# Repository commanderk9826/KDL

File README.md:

국민대학교 24EV KUST 데이터로거팀

KUST Data Logger 제작 프로젝트
참여자 : 이채훈, 옹미령, 강호, 이지규

PCB제작 : 고민제

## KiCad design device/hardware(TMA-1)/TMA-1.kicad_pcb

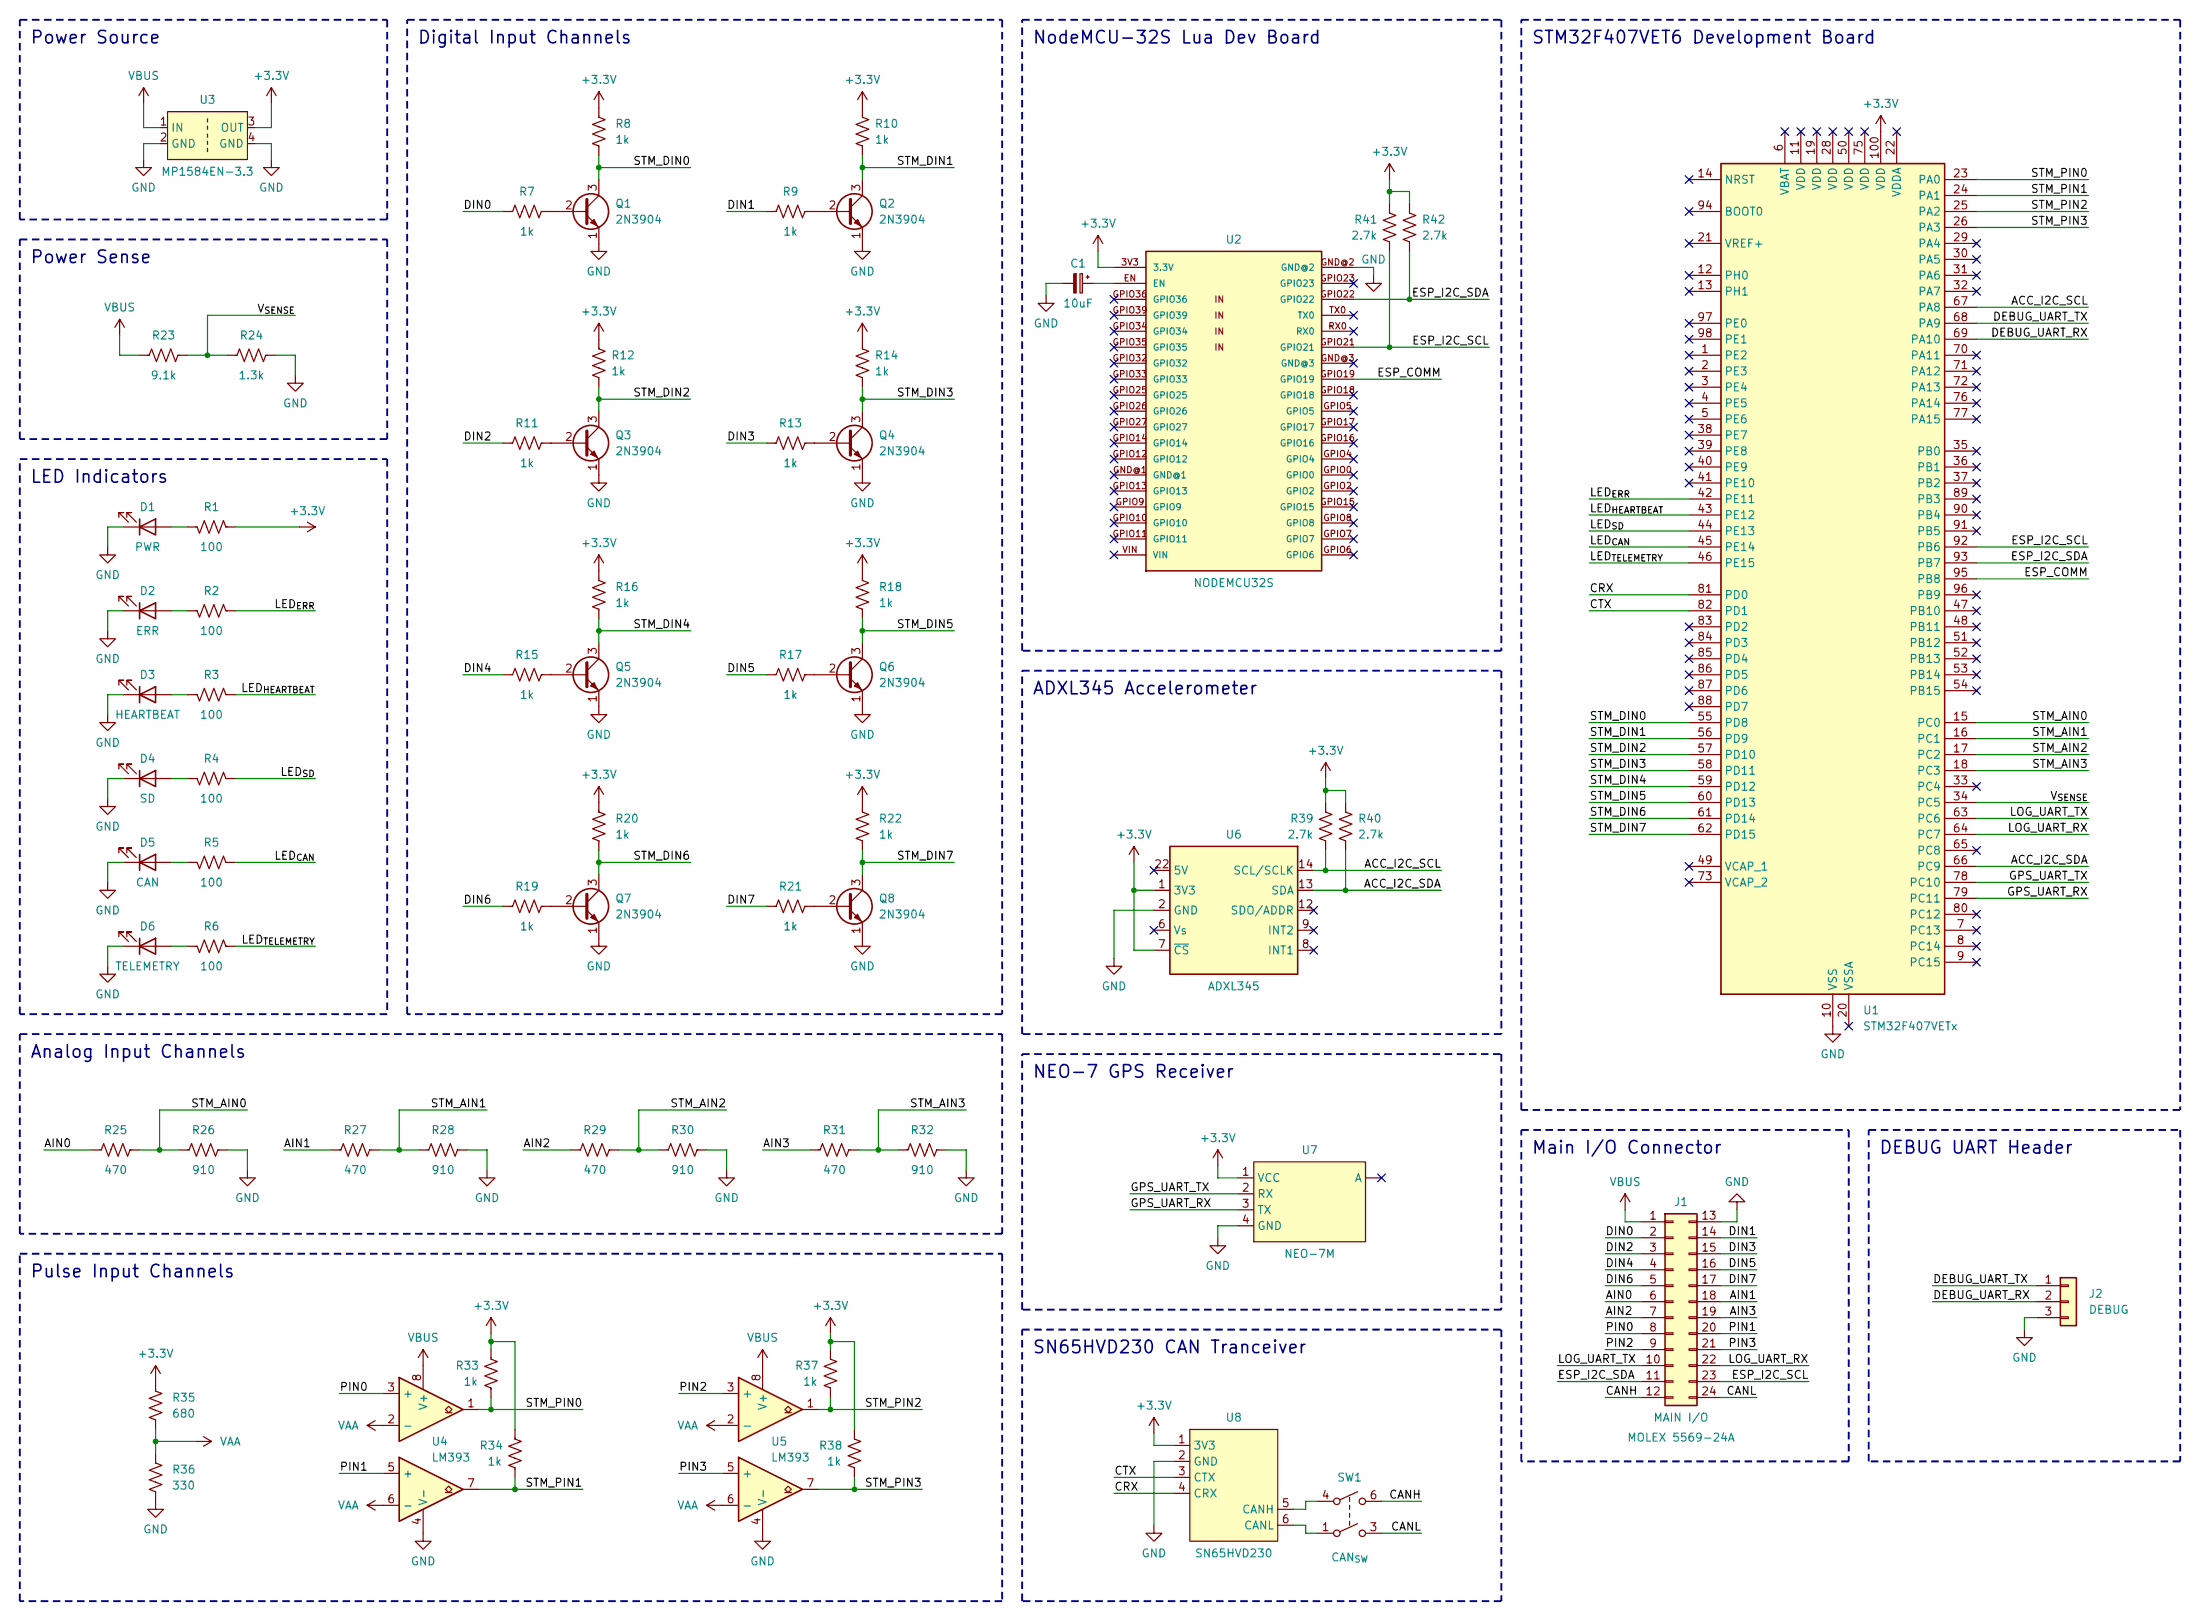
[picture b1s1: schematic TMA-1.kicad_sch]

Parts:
C1: 10uF; CP_Radial_D5.0mm_P2.00mm
D1: PWR; LED_D5.0mm_FlatTop
D2: ERR; LED_D5.0mm_FlatTop
D3: HEARTBEAT; LED_D5.0mm_FlatTop
D4: SD; LED_D5.0mm_FlatTop
D5: CAN; LED_D5.0mm_FlatTop
D6: TELEMETRY; LED_D5.0mm_FlatTop
J1: MAIN I/O; Molex_Mini-Fit_Jr_5569-24A1_2x12_P4.20mm_Horizontal
J2: DEBUG; PinHeader_1x03_P2.54mm_Vertical
Q1, Q2, Q3, Q4, Q5, Q6, Q7, Q8: 2N3904; TO-92_Inline_Wide
R1, R2, R3, R4, R5, R6: 100; R_Axial_DIN0207_L6.3mm_D2.5mm_P10.16mm_Horizontal
R7, R8, R9, R10, R11, R12, R13, R14, R15, R16, R17, R18, R19, R20, R21, R22, R33, R34, R37, R38: 1k; R_Axial_DIN0207_L6.3mm_D2.5mm_P10.16mm_Horizontal
R23: 9.1k; R_Axial_DIN0207_L6.3mm_D2.5mm_P10.16mm_Horizontal
R24: 1.3k; R_Axial_DIN0207_L6.3mm_D2.5mm_P10.16mm_Horizontal
R25, R27, R29, R31: 470; R_Axial_DIN0207_L6.3mm_D2.5mm_P10.16mm_Horizontal
R26, R28, R30, R32: 910; R_Axial_DIN0207_L6.3mm_D2.5mm_P10.16mm_Horizontal
R35: 680; R_Axial_DIN0207_L6.3mm_D2.5mm_P10.16mm_Horizontal
R36: 330; R_Axial_DIN0207_L6.3mm_D2.5mm_P10.16mm_Horizontal
R39, R40, R41, R42: 2.7k; R_Axial_DIN0207_L6.3mm_D2.5mm_P10.16mm_Horizontal
SW1: CAN_{SW}; TOGGLE_SWITCH
U1: STM32F407VETx; STM32F407_HOLDER
U2: NODEMCU32S
U3: MP1584EN-3.3; MP1584EN_MODULE
U4, U5: LM393; DIP-8_W7.62mm
U6: ADXL345; ADXL345_MODULE
U7: NEO-7M; GPS_MODULE
U8: SN65HVD230; SN65HVD230_MODULE

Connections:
+3.3V: R1.1, R8.1, R10.1, R12.1, R14.1, R16.1, R18.1, R20.1, R22.1, R33.1, R34.1, R35.1, R37.1, R38.1, R39.1, R40.1, R41.1, R42.1, U1.100 (VDD), U2.3V3 (3.3V), U3.3 (OUT), U6.1 (3V3), U6.7 (~CS), U7.1 (VCC), U8.1 (3V3)
/ACC_I2C_SCL: R39.2, U1.67 (PA8), U6.14 (SCL/SCLK)
/ACC_I2C_SDA: R40.2, U1.66 (PC9), U6.13 (SDA)
/AIN0: J1.6, R25.1
/AIN1: J1.18, R27.1
/AIN2: J1.7, R29.1
/AIN3: J1.19, R31.1
/CANH: J1.12, SW1.6
/CANL: J1.24, SW1.3
/CRX: U1.81 (PD0), U8.4 (CRX)
/CTX: U1.82 (PD1), U8.3 (CTX)
/DEBUG_UART_RX: J2.2, U1.69 (PA10)
/DEBUG_UART_TX: J2.1, U1.68 (PA9)
/DIN0: J1.2, R7.1
/DIN1: J1.14, R9.1
/DIN2: J1.3, R11.1
/DIN3: J1.15, R13.1
/DIN4: J1.4, R15.1
/DIN5: J1.16, R17.1
/DIN6: J1.5, R19.1
/DIN7: J1.17, R21.1
/ESP_COMM: U1.95 (PB8), U2.GPIO19
/ESP_I2C_SCL: J1.23, R41.2, U1.92 (PB6), U2.GPIO21
/ESP_I2C_SDA: J1.11, R42.2, U1.93 (PB7), U2.GPIO22
/GPS_UART_RX: U1.79 (PC11), U7.3 (TX)
/GPS_UART_TX: U1.78 (PC10), U7.2 (RX)
/LED_{CAN}: R5.1, U1.45 (PE14)
/LED_{ERR}: R2.1, U1.42 (PE11)
/LED_{HEARTBEAT}: R3.1, U1.43 (PE12)
/LED_{SD}: R4.1, U1.44 (PE13)
/LED_{TELEMETRY}: R6.1, U1.46 (PE15)
/LOG_UART_RX: J1.22, U1.64 (PC7)
/LOG_UART_TX: J1.10, U1.63 (PC6)
/PIN0: J1.8, U4.3 (+)
/PIN1: J1.20, U4.5 (+)
/PIN2: J1.9, U5.3 (+)
/PIN3: J1.21, U5.5 (+)
/STM_AIN0: R25.2, R26.1, U1.15 (PC0)
/STM_AIN1: R27.2, R28.1, U1.16 (PC1)
/STM_AIN2: R29.2, R30.1, U1.17 (PC2)
/STM_AIN3: R31.2, R32.1, U1.18 (PC3)
/STM_DIN0: Q1.3 (C), R8.2, U1.55 (PD8)
/STM_DIN1: Q2.3 (C), R10.2, U1.56 (PD9)
/STM_DIN2: Q3.3 (C), R12.2, U1.57 (PD10)
/STM_DIN3: Q4.3 (C), R14.2, U1.58 (PD11)
/STM_DIN4: Q5.3 (C), R16.2, U1.59 (PD12)
/STM_DIN5: Q6.3 (C), R18.2, U1.60 (PD13)
/STM_DIN6: Q7.3 (C), R20.2, U1.61 (PD14)
/STM_DIN7: Q8.3 (C), R22.2, U1.62 (PD15)
/STM_PIN0: R33.2, U1.23 (PA0), U4.1
/STM_PIN1: R34.2, U1.24 (PA1), U4.7
/STM_PIN2: R37.2, U1.25 (PA2), U5.1
/STM_PIN3: R38.2, U1.26 (PA3), U5.7
/V_{SENSE}: R23.2, R24.1, U1.34 (PC5)
GND: C1.2, D1.1 (K), D2.1 (K), D3.1 (K), D4.1 (K), D5.1 (K), D6.1 (K), J1.13, J2.3, Q1.1 (E), Q2.1 (E), Q3.1 (E), Q4.1 (E), Q5.1 (E), Q6.1 (E), Q7.1 (E), Q8.1 (E), R24.2, R26.2, R28.2, R30.2, R32.2, R36.2, U1.10 (VSS), U1.27 (VSS), U1.74 (VSS), U1.99 (VSS), U2.GND@2, U3.2 (GND), U3.4 (GND), U4.4 (V-), U5.4 (V-), U6.2 (GND), U7.4 (GND), U8.2 (GND)
unnamed: C1.1, U2.EN
unnamed: D1.2 (A), R1.2
unnamed: D2.2 (A), R2.2
unnamed: D3.2 (A), R3.2
unnamed: D4.2 (A), R4.2
unnamed: D5.2 (A), R5.2
unnamed: D6.2 (A), R6.2
unnamed: Q1.2 (B), R7.2
unnamed: Q2.2 (B), R9.2
unnamed: Q3.2 (B), R11.2
unnamed: Q4.2 (B), R13.2
unnamed: Q5.2 (B), R15.2
unnamed: Q6.2 (B), R17.2
unnamed: Q7.2 (B), R19.2
unnamed: Q8.2 (B), R21.2
unnamed: SW1.4, U8.5 (CANH)
unnamed: SW1.1, U8.6 (CANL)
VAA: R35.2, R36.1, U4.2 (-), U4.6 (-), U5.2 (-), U5.6 (-)
VBUS: J1.1, R23.1, U3.1 (IN), U4.8 (V+), U5.8 (V+)

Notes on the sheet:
LED Indicators
Power Source
Main I/O Connector
Digital Input Channels
STM32F407VET6 Development Board
DEBUG UART Header
NEO-7 GPS Receiver
Power Sense
Analog Input Channels
Pulse Input Channels
ADXL345 Accelerometer
SN65HVD230 CAN Tranceiver
NodeMCU-32S Lua Dev Board

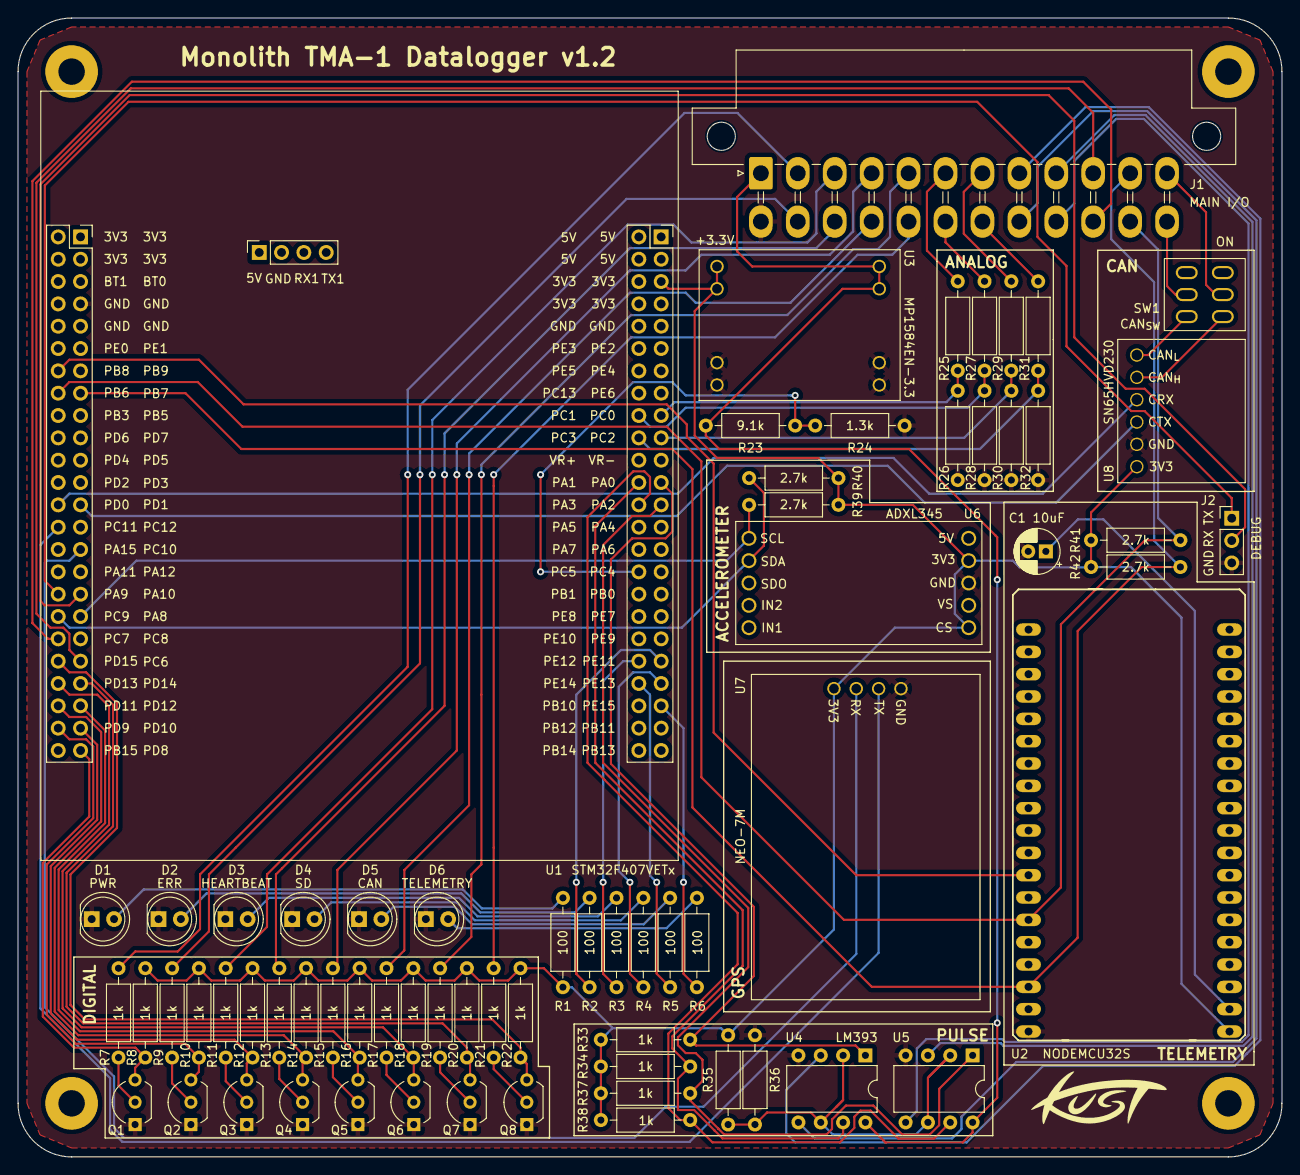
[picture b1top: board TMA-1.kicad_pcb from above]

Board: 2 copper layers, 143.8 x 129.5 mm, 68 parts (0 on the bottom side), 74 nets.

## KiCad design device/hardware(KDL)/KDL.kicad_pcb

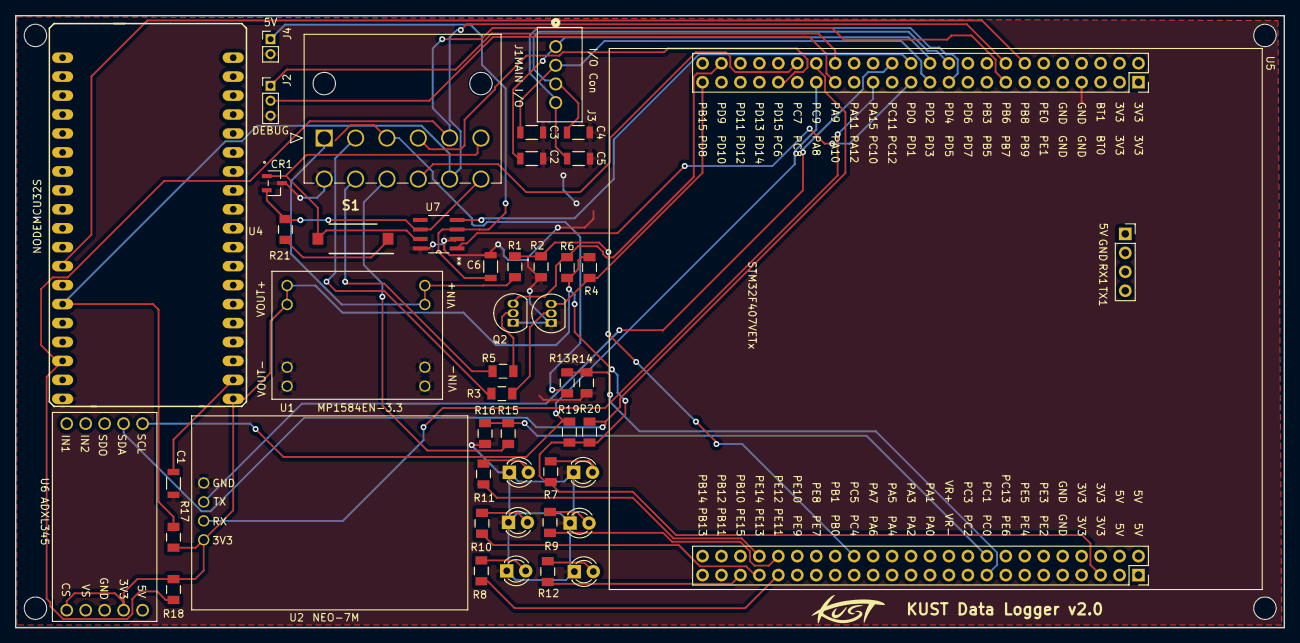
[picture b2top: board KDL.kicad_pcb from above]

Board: 2 copper layers, 170.0 x 82.0 mm, 47 parts (0 on the bottom side), 47 nets.

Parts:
C1: 10uF; CAP_CL31_SAM
C2, C3, C4, C5: 1uF; CAP_CL31_SAM
C6: 0.1uF; CAP_CL31_SAM
CR1: CDSOT23-T24CAN; SOT23-3L_STM
D1: PWR; LED_D3.0mm
D2: ERR; LED_D3.0mm
D3: HEARTBEAT; LED_D3.0mm
D4: SD; LED_D3.0mm
D5: CAN; LED_D3.0mm
D6: TELEMETRY; LED_D3.0mm
J1: MAIN I/O; CON_39301121
J2: DEBUG; PinHeader_1x03_P2.00mm_Vertical
J3: I/O Con; CONN_B4B-XH-A_JST
J4: 5V; PinHeader_1x02_P2.00mm_Vertical
Q1, Q2: 2N3904; TO-92_Inline
R1: 9.1k; RC1206N_YAG
R2: 1.3k; RC1206N_YAG
R3, R4, R5, R6: 1k; RC1206N_YAG
R7, R8, R9, R10, R11, R12: 220; RC1206N_YAG
R13, R15: 470; RC1206N_YAG
R14, R16: 910; RC1206N_YAG
R17, R18: 2.7k; RC1206N_YAG
R19, R20: 2.7K; RC1206N_YAG
R21: 120k; RC1206N_YAG
S1: CFS-0102MB; SOD10040X470N
U1: MP1584EN-3.3; MP1584EN_MODULE
U2: NEO-7M; GPS_MODULE
U4: NODEMCU32S
U5: STM32F407VETx; STM32F407_HOLDER
U6: ADXL345; ADXL345_MODULE
U7: SN65HVD1050DR; D8

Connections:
+3.3V: R4.1, R6.1, R7.2, R17.1, R18.1, R19.2, R20.2, U1.3 (OUT), U2.1 (VCC), U4.3V3 (3.3V), U5.100 (VDD), U6.1 (3V3), U6.7 (~CS)
/5V: C6.2, J4.1, U7.3 (VCC)
/ACC_I2C_SCL: R19.1, U5.67 (PA8), U6.14 (SCL/SCLK)
/ACC_I2C_SDA: R20.1, U5.66 (PC9), U6.13 (SDA)
/AIN0: J1.3, R13.1
/AIN1: J1.9, R15.1
/CANH: CR1.1, J1.6, S1.2, U7.7 (CANH)
/CANL: CR1.2, J1.12, R21.1, U7.6 (CANL)
/CRX: U5.81 (PD0), U7.4 (RXD)
/CTX: U5.82 (PD1), U7.1 (TXD)
/DEBUG_UART_RX: J2.2, U5.69 (PA10)
/DEBUG_UART_TX: J2.1, U5.68 (PA9)
/DIN0: J1.2, R3.2
/DIN1: J1.8, R5.2
/ESP_COMM: U4.GPIO19, U5.95 (PB8)
/ESP_I2C_SCL: J1.11, R17.2, U4.GPIO21, U5.92 (PB6)
/ESP_I2C_SDA: J1.5, R18.2, U4.GPIO22, U5.93 (PB7)
/GPS_UART_RX: U2.3 (TX), U5.79 (PC11)
/GPS_UART_TX: U2.2 (RX), U5.78 (PC10)
/IO1: C2.2, J3.1, U5.83 (PD2)
/IO2: C3.2, J3.2, U5.84 (PD3)
/IO3: C4.2, J3.3, U5.85 (PD4)
/IO4: C5.2, J3.4, U5.86 (PD5)
/LED_CAN: R11.2, U5.45 (PE14)
/LED_ERR: R8.2, U5.42 (PE11)
/LED_HEARTBEAT: R9.2, U5.43 (PE12)
/LED_SD: R10.2, U5.44 (PE13)
/LED_TELEMETRY: R12.2, U5.46 (PE15)
/LOG_UART_RX: J1.10, U5.64 (PC7)
/LOG_UART_TX: J1.4, U5.63 (PC6)
/STM_AIN0: R13.2, R14.1, U5.15 (PC0)
/STM_AIN1: R15.2, R16.1, U5.16 (PC1)
/STM_DIN0: Q1.3 (C), R4.2, U5.55 (PD8)
/STM_DIN1: Q2.3 (C), R6.2, U5.56 (PD9)
/VSENSE: R1.2, R2.1, U5.34 (PC5)
GND: C1.1, C2.1, C3.1, C4.1, C5.1, C6.1, CR1.3, D1.1 (K), D2.1 (K), D3.1 (K), D4.1 (K), D5.1 (K), D6.1 (K), J1.7, J2.3, J4.2, Q1.1 (E), Q2.1 (E), R2.2, R14.2, R16.2, U1.2 (GND), U1.4 (GND), U2.4 (GND), U4.GND@2, U5.10 (VSS), U6.2 (GND), U7.2 (GND), U7.8 (S)
unnamed: C1.2, U4.EN
unnamed: D1.2 (A), R7.1
unnamed: D2.2 (A), R8.1
unnamed: D3.2 (A), R9.1
unnamed: D4.2 (A), R10.1
unnamed: D5.2 (A), R11.1
unnamed: D6.2 (A), R12.1
unnamed: Q1.2 (B), R3.1
unnamed: Q2.2 (B), R5.1
unnamed: R21.2, S1.1
VBUS: J1.1, R1.1, U1.1 (IN)

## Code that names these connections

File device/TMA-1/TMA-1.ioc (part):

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Mcu.Name=STM32F407V(E-G)Tx
Mcu.Package=LQFP100
Mcu.UserName=STM32F407VETx
PA0-WKUP.GPIOParameters=GPIO_Label
PA0-WKUP.GPIO_Label=PIN0
PA0-WKUP.Signal=S_TIM5_CH1
PA1.GPIOParameters=GPIO_Label
PA1.GPIO_Label=PIN1
PA1.Signal=S_TIM5_CH2
PA10.GPIOParameters=GPIO_Label
PA10.GPIO_Label=USART_DEBUG_RX
PA10.Mode=Asynchronous
PA10.Signal=USART1_RX
PA2.GPIOParameters=GPIO_Label
PA2.GPIO_Label=PIN2
PA2.Signal=S_TIM5_CH3
PA3.GPIOParameters=GPIO_Label
PA3.GPIO_Label=PIN3
PA3.Signal=S_TIM5_CH4
PA6.GPIOParameters=GPIO_PuPd,GPIO_Label
PA6.GPIO_Label=LED_ONBOARD_0
PA6.GPIO_PuPd=GPIO_PULLDOWN
PA6.Signal=GPIO_Output
PA7.GPIOParameters=GPIO_PuPd,GPIO_Label
PA7.GPIO_Label=LED_ONBOARD_1
PA7.GPIO_PuPd=GPIO_PULLDOWN
PA7.Signal=GPIO_Output
PA8.GPIOParameters=GPIO_Label
PA8.GPIO_Label=I2C_ACC_SCL
PA8.Mode=I2C
PA8.Signal=I2C3_SCL
PA9.GPIOParameters=GPIO_Label
PA9.GPIO_Label=USART_DEBUG_TX
PA9.Mode=Asynchronous
PA9.Signal=USART1_TX
PB12.GPIOParameters=GPIO_PuPd,GPIO_Label
PB12.GPIO_Label=SDIO_DETECT
PB12.GPIO_PuPd=GPIO_PULLDOWN
PB12.Signal=GPIO_Input
PB6.GPIOParameters=GPIO_Label
PB6.GPIO_Label=I2C_ESP_SCL
PB6.Mode=I2C
PB6.Signal=I2C1_SCL
PB7.GPIOParameters=GPIO_Label
PB7.GPIO_Label=I2C_ESP_SDA
PB7.Mode=I2C
PB7.Signal=I2C1_SDA
PB8.GPIOParameters=GPIO_Label,GPIO_ModeDefaultEXTI
PB8.GPIO_Label=ESP_COMM
PB8.GPIO_ModeDefaultEXTI=GPIO_MODE_IT_RISING_FALLING
PB8.Signal=GPXTI8
PC0.GPIOParameters=GPIO_Label
PC0.GPIO_Label=AIN0
PC0.Signal=ADCx_IN10
PC1.GPIOParameters=GPIO_Label
PC1.GPIO_Label=AIN1
PC1.Signal=ADCx_IN11
PC10.GPIOParameters=GPIO_Label
PC10.GPIO_Label=USART_GPS_TX
PC10.Mode=Asynchronous
PC10.Signal=USART3_TX
PC11.GPIOParameters=GPIO_Label
PC11.GPIO_Label=USART_GPS_RX
PC11.Mode=Asynchronous
PC11.Signal=USART3_RX
PC12.Mode=SD_1_bit
PC12.Signal=SDIO_CK
PC14-OSC32_IN.Mode=LSE-External-Oscillator
PC14-OSC32_IN.Signal=RCC_OSC32_IN
PC15-OSC32_OUT.Mode=LSE-External-Oscillator
PC15-OSC32_OUT.Signal=RCC_OSC32_OUT
PC2.GPIOParameters=GPIO_Label
PC2.GPIO_Label=AIN2
PC2.Signal=ADCx_IN12
PC3.GPIOParameters=GPIO_Label
PC3.GPIO_Label=AIN3
PC3.Signal=ADCx_IN13
PC5.GPIOParameters=GPIO_Label
PC5.GPIO_Label=Vsense
PC5.Signal=ADCx_IN15
PC6.GPIOParameters=GPIO_Label
PC6.GPIO_Label=USART_LOG_TX
PC6.Mode=Asynchronous
PC6.Signal=USART6_TX
PC7.GPIOParameters=GPIO_Label
PC7.GPIO_Label=USART_LOG_RX
PC7.Mode=Asynchronous
PC7.Signal=USART6_RX
PC8.GPIOParameters=GPIO_PuPd
PC8.GPIO_PuPd=GPIO_PULLUP
PC8.Mode=SD_1_bit
PC8.Signal=SDIO_D0
PC9.GPIOParameters=GPIO_Label
PC9.GPIO_Label=I2C_ACC_SDA
PC9.Mode=I2C
PC9.Signal=I2C3_SDA
PD0.Mode=CAN_Activate
PD0.Signal=CAN1_RX
PD1.Mode=CAN_Activate
PD1.Signal=CAN1_TX
PD10.GPIOParameters=GPIO_PuPd,GPIO_Label
PD10.GPIO_Label=DIN2
PD10.GPIO_PuPd=GPIO_PULLDOWN
PD10.Signal=GPIO_Input
PD11.GPIOParameters=GPIO_PuPd,GPIO_Label
PD11.GPIO_Label=DIN3
PD11.GPIO_PuPd=GPIO_PULLDOWN
PD11.Signal=GPIO_Input
PD12.GPIOParameters=GPIO_PuPd,GPIO_Label
PD12.GPIO_Label=DIN4
PD12.GPIO_PuPd=GPIO_PULLDOWN
PD12.Signal=GPIO_Input
PD13.GPIOParameters=GPIO_PuPd,GPIO_Label
PD13.GPIO_Label=DIN5
PD13.GPIO_PuPd=GPIO_PULLDOWN
PD13.Signal=GPIO_Input
PD14.GPIOParameters=GPIO_PuPd,GPIO_Label
PD14.GPIO_Label=DIN6
PD14.GPIO_PuPd=GPIO_PULLDOWN
PD14.Signal=GPIO_Input
PD15.GPIOParameters=GPIO_PuPd,GPIO_Label
PD15.GPIO_Label=DIN7
PD15.GPIO_PuPd=GPIO_PULLDOWN
PD15.Signal=GPIO_Input
PD2.GPIOParameters=GPIO_PuPd
PD2.GPIO_PuPd=GPIO_PULLUP
PD2.Mode=SD_1_bit
PD2.Signal=SDIO_CMD
PD8.GPIOParameters=GPIO_PuPd,GPIO_Label
PD8.GPIO_Label=DIN0
PD8.GPIO_PuPd=GPIO_PULLDOWN
PD8.Signal=GPIO_Input
PD9.GPIOParameters=GPIO_PuPd,GPIO_Label
PD9.GPIO_Label=DIN1
PD9.GPIO_PuPd=GPIO_PULLDOWN
PD9.Signal=GPIO_Input
PE10.GPIOParameters=GPIO_Label
PE10.GPIO_Label=LED_CUSTOM_1
PE10.Signal=GPIO_Output
PE11.GPIOParameters=GPIO_Label
PE11.GPIO_Label=LED_ERR
PE11.Signal=GPIO_Output
PE12.GPIOParameters=GPIO_Label
PE12.GPIO_Label=LED_HEARTBEAT
PE12.Signal=GPIO_Output
PE13.GPIOParameters=GPIO_Label
PE13.GPIO_Label=LED_SD
PE13.Signal=GPIO_Output
PE14.GPIOParameters=GPIO_Label
PE14.GPIO_Label=LED_CAN
PE14.Signal=GPIO_Output
PE15.GPIOParameters=GPIO_Label
PE15.GPIO_Label=LED_TELEMETRY
PE15.Signal=GPIO_Output
PE9.GPIOParameters=GPIO_Label
PE9.GPIO_Label=LED_CUSTOM_0
PE9.Signal=GPIO_Output
PH0-OSC_IN.Mode=HSE-External-Oscillator
PH0-OSC_IN.Signal=RCC_OSC_IN
PH1-OSC_OUT.Mode=HSE-External-Oscillator
PH1-OSC_OUT.Signal=RCC_OSC_OUT
RCC.HSE_VALUE=8000000
RCC.SYSCLKFreq_VALUE=168000000
RCC.SYSCLKSource=RCC_SYSCLKSOURCE_PLLCLK
board=custom
